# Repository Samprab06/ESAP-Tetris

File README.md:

# ESAP Tetris

A complete, feature-packed Tetris game implementation for the ESP32 microcontroller featuring a custom PCB design, real-time graphics rendering on an ILI9341 SPI TFT display, I2S audio playback, SD card asset loading and a future multiplayer implementation

---

##  PCB Design

The project features a custom-designed PCB tailored for handheld gameplay with optimized power delivery, hardware debouncing, and an auto-programming USB-C interface.

### Board Renders

| Back View (Component Side) | Front View (Controls) |
| :---: | :---: |
|  |  |

### Key Hardware & Schematic Highlights

- **Microcontroller**: ESP32-WROOM-32 module (32-bit dual-core Xtensa @ 240 MHz, 520 KB SRAM, Wi-Fi/BT).
- **USB-C Interface & Auto-Flashing**: Integrated `CH340C` USB-to-UART converter with dual NPN auto-reset circuitry (`MUN5211DW1`) for seamless hands-free code uploads via USB Type-C.
- **Power Management**: `AP2112K-3.3` LDO regulator supplying up to 600mA at 3.3V with dedicated ground plane thermal heat sinking. USB Type-C `CC1`/`CC2` 5.1kΩ pull-down resistors for 5V C-to-C charger support.
- **Display Connection**: Dedicated 14-pin socket header for 2.8" ILI9341 SPI TFT Display (240×320 resolution) on the `VSPI` bus. Includes 10kΩ pull-up resistor on `CS` (`GPIO5`).
- **SD Card Storage**: 4-pin SPI socket header for MicroSD card module on the `HSPI` bus. Includes 10kΩ pull-up resistor on `CS` (`GPIO15`).
- **Input Controllers**: 8 tactile pushbuttons (UP, DOWN, LEFT, RIGHT, A, B, START, SELECT) with hardware RC debouncing filters (0.1µF capacitors) and 10kΩ pull-up resistors on input-only GPIOs (34, 35, 36, 39).
- **Audio & Volume Control**: Audio output header with an integrated slide switch (`SW12`) for hardware gain/volume control.

---

## 🛠️ Hardware Specifications & Pinout

### SPI Display Connection (VSPI)

| ESP32 Pin | Signal Name | Display Function |
| :--- | :--- | :--- |
| **GPIO 23** | `MOSI` | Serial Data Input |
| **GPIO 19** | `MISO` | Serial Data Output |
| **GPIO 18** | `SCK` | Serial Clock |
| **GPIO 5** | `CS` | Chip Select (10kΩ Pull-Up) |
| **GPIO 2** | `DC` | Data / Command Select |
| **GPIO 4** | `RST` | Reset |
| **3.3V** | `LED` | Display Backlight Power |

### MicroSD Card Connection (HSPI)

| ESP32 Pin | Signal Name | SD Card Function |
| :--- | :--- | :--- |
| **GPIO 13** | `MOSI` | Data Input |
| **GPIO 17** | `MISO` | Data Output |
| **GPIO 14** | `SCK` | Clock |
| **GPIO 15** | `CS` | Chip Select (10kΩ Pull-Up) |

### Game Control Buttons

| GPIO Pin | Function | Hardware Circuit |
| :--- | :--- | :--- |
| **GPIO 36 (VP)** | Left | 10kΩ Pull-Up + 0.1µF Debounce |
| **GPIO 39 (VN)** | Right | 10kΩ Pull-Up + 0.1µF Debounce |
| **GPIO 34** | Down | 10kΩ Pull-Up + 0.1µF Debounce |
| **GPIO 35** | Up / Rotate | 10kΩ Pull-Up + 0.1µF Debounce |
| **GPIO 32** | Button A | 10kΩ Pull-Up + 0.1µF Debounce |
| **GPIO 33** | Button B | 10kΩ Pull-Up + 0.1µF Debounce |
| **GPIO 27** | Start | 10kΩ Pull-Up + 0.1µF Debounce |
| **GPIO 16** | Select | 10kΩ Pull-Up + 0.1µF Debounce |

---

##  Software Architecture

The software is structured as a **PlatformIO** project 

```
ESAP_Tetris/
├── PCB/                     # KiCad 10 PCB schematics, board layouts & gerbers
│   ├── pcb_front.png
│   └── pcb_back.png
├── include/                 # Header files
│   ├── main.hpp
│   ├── logic.h
│   ├── display.h
│   ├── audio.h
│   └── sdcard.h
├── src/                     # Source implementations
│   ├── main.cpp             # FreeRTOS task initialization & main loop
│   ├── logic.cpp            # Tetris game rules & state machine
│   ├── display.cpp          # TFT graphics rendering
│   ├── audio.cpp            # I2S audio decoding & streaming
│   └── sdcard.cpp           # SD card file system interface
├── platformio.ini           # PlatformIO configuration
└── README.md                # Project documentation
```

---

##  Building & Flashing

### Prerequisites
- **VS Code** with **PlatformIO IDE** extension installed.

### Steps
1. Clone the repository:
   ```bash
   git clone https://github.com/Samprab06/ESAP-Tetris.git
   cd ESAP-Tetris
   ```
2. Connect your ESP32 board via USB-C.
3. Build & Upload firmware using PlatformIO:
   ```bash
   pio run -t upload
   ```
4. Open the Serial Monitor:
   ```bash
   pio device monitor
   ```

---

---

##  License

This project is open-source and provided for educational and personal use.

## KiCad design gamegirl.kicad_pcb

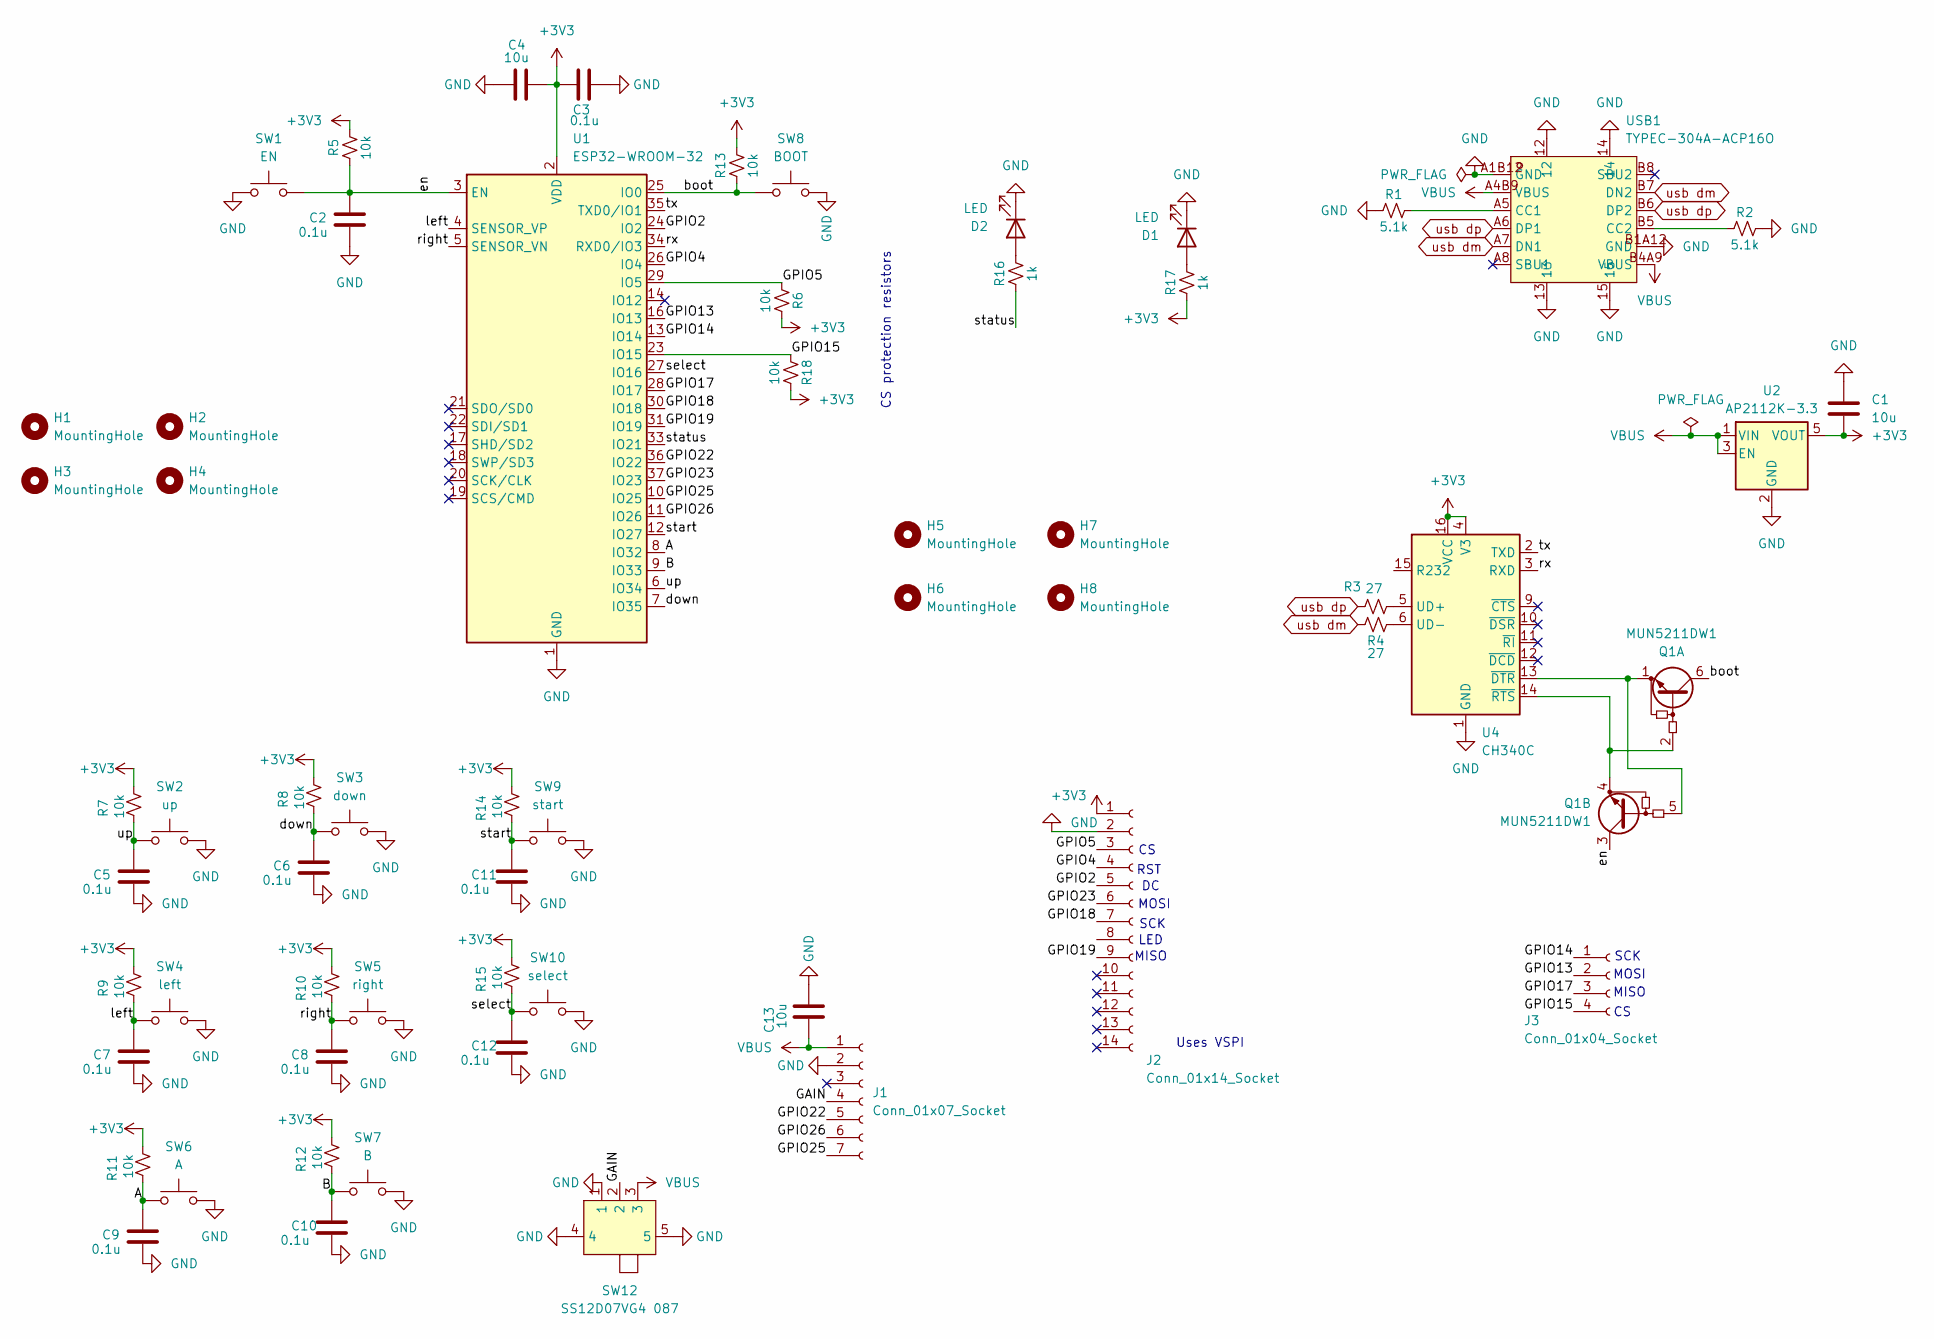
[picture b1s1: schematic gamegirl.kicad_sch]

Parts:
C1, C4, C13: 10u; C_0805_2012Metric
C2, C3, C5, C6, C7, C8, C9, C10, C11, C12: 0.1u; C_0805_2012Metric
D1, D2: LED; LED_0603_1608Metric
H1, H2, H3, H4: MountingHole; MountingHole_3.2mm_M3
H5, H6, H7, H8: MountingHole; MountingHole_3.2mm_M3_DIN965_Pad
J1: Conn_01x07_Socket; PinSocket_1x07_P2.54mm_Vertical
J2: Conn_01x14_Socket; PinSocket_1x14_P2.54mm_Vertical
J3: Conn_01x04_Socket; PinSocket_1x04_P2.54mm_Vertical
Q1: MUN5211DW1; SOT-363_SC-70-6
R1, R2: 5.1k; R_0805_2012Metric
R3, R4: 27; R_0603_1608Metric
R5, R6, R7, R8, R9, R10, R11, R12, R13, R14, R15, R18: 10k; R_0805_2012Metric
R16, R17: 1k; R_0805_2012Metric
SW1: EN; SW_PUSH_6mm
SW2: up; SW_PUSH_6mm
SW3: down; SW_PUSH_6mm
SW4: left; SW_PUSH_6mm
SW5: right; SW_PUSH_6mm
SW6: A; SW_PUSH_6mm
SW7: B; SW_PUSH_6mm
SW8: BOOT; SW_PUSH_6mm
SW9: start; SW_PUSH_6mm
SW10: select; SW_PUSH_6mm
SW12: SS12D07VG4 087; SW-TH_SS12D07VG4; MPN SS12D07VG4 087; LCSC Part C2939726
U1: ESP32-WROOM-32
U2: AP2112K-3.3; SOT-23-5
U4: CH340C; SOIC-16_3.9x9.9mm_P1.27mm
USB1: TYPEC-304A-ACP16O; USB-SMD_TYPEC-304A-ACP16O; MPN TYPEC-304A-ACP16O; LCSC Part C2909610

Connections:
+3V3: C1.2, C3.1, C4.2, J2.1, R5.2, R6.2, R7.2, R8.2, R9.2, R10.2, R11.2, R12.2, R13.2, R14.2, R15.2, R17.1, R18.2, U1.2 (VDD), U2.5 (VOUT), U4.4 (V3), U4.16 (VCC)
/A: C9.1, R11.1, SW6.1, U1.8 (IO32)
/B: C10.1, R12.1, SW7.1, U1.9 (IO33)
/GAIN: J1.4, SW12.2
/GPIO2: J2.5, U1.24 (IO2)
/GPIO4: J2.4, U1.26 (IO4)
/GPIO5: J2.3, R6.1, U1.29 (IO5)
/GPIO13: J3.2, U1.16 (IO13)
/GPIO14: J3.1, U1.13 (IO14)
/GPIO15: J3.4, R18.1, U1.23 (IO15)
/GPIO17: J3.3, U1.28 (IO17)
/GPIO18: J2.7, U1.30 (IO18)
/GPIO19: J2.9, U1.31 (IO19)
/GPIO22: J1.5, U1.36 (IO22)
/GPIO23: J2.6, U1.37 (IO23)
/GPIO25: J1.7, U1.10 (IO25)
/GPIO26: J1.6, U1.11 (IO26)
/boot: Q1.6 (C1), R13.1, SW8.1, U1.25 (IO0)
/down: C6.1, R8.1, SW3.1, U1.7 (IO35)
/en: C2.1, Q1.3 (C2), R5.1, SW1.2, U1.3 (EN)
/left: C7.1, R9.1, SW4.1, U1.4 (SENSOR_VP)
/right: C8.1, R10.1, SW5.1, U1.5 (SENSOR_VN)
/rx: U1.34 (RXD0/IO3), U4.3 (RXD)
/select: C12.1, R15.1, SW10.1, U1.27 (IO16)
/start: C11.1, R14.1, SW9.1, U1.12 (IO27); also elsewhere on the board
/status: R16.1, U1.33 (IO21)
/tx: U1.35 (TXD0/IO1), U4.2 (TXD)
/up: C5.1, R7.1, SW2.1, U1.6 (IO34)
GND: C1.1, C2.2, C3.2, C4.1, C5.2, C6.2, C7.2, C8.2, C9.2, C10.2, C11.2, C12.2, C13.2, D1.1 (K), D2.1 (K), J1.2, J2.2, R1.1, R2.2, SW1.1, SW2.2, SW3.2, SW4.2, SW5.2, SW6.2, SW7.2, SW8.2, SW9.2, SW10.2, SW12.1, SW12.4, SW12.5, U1.1 (GND), U1.15 (GND), U1.38 (GND), U1.39 (GND), U2.2 (GND), U4.1 (GND), USB1.12, USB1.13, USB1.14, USB1.15, USB1.A1B12 (GND), USB1.B1A12 (GND); also elsewhere on the board
unnamed: D1.2 (A), R17.2
unnamed: D2.2 (A), R16.2
unnamed: Q1.2 (B1), Q1.4 (E2), U4.14 (~RTS)
unnamed: Q1.1 (E1), Q1.5 (B2), U4.13 (~DTR)
unnamed: R3.2, U4.5 (UD+)
unnamed: R4.2, U4.6 (UD-)
unnamed: R1.2, USB1.A5 (CC1)
unnamed: R2.1, USB1.B5 (CC2)
VBUS: C13.1, J1.1, SW12.3, U2.1 (VIN), U2.3 (EN), USB1.A4B9 (VBUS), USB1.B4A9 (VBUS)
usb dm: R4.1, USB1.A7 (DN1), USB1.B7 (DN2)
usb dp: R3.1, USB1.A6 (DP1), USB1.B6 (DP2)

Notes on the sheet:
MISO
SCK
CS protection resistors
Uses VSPI
MOSI
LED
RST

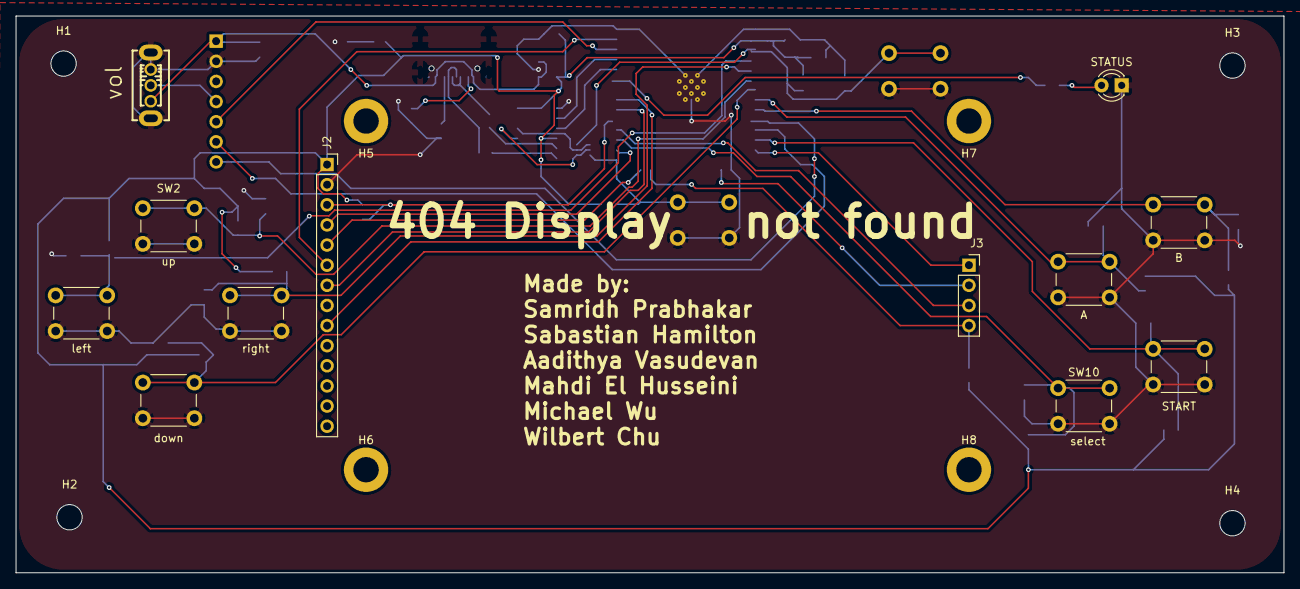
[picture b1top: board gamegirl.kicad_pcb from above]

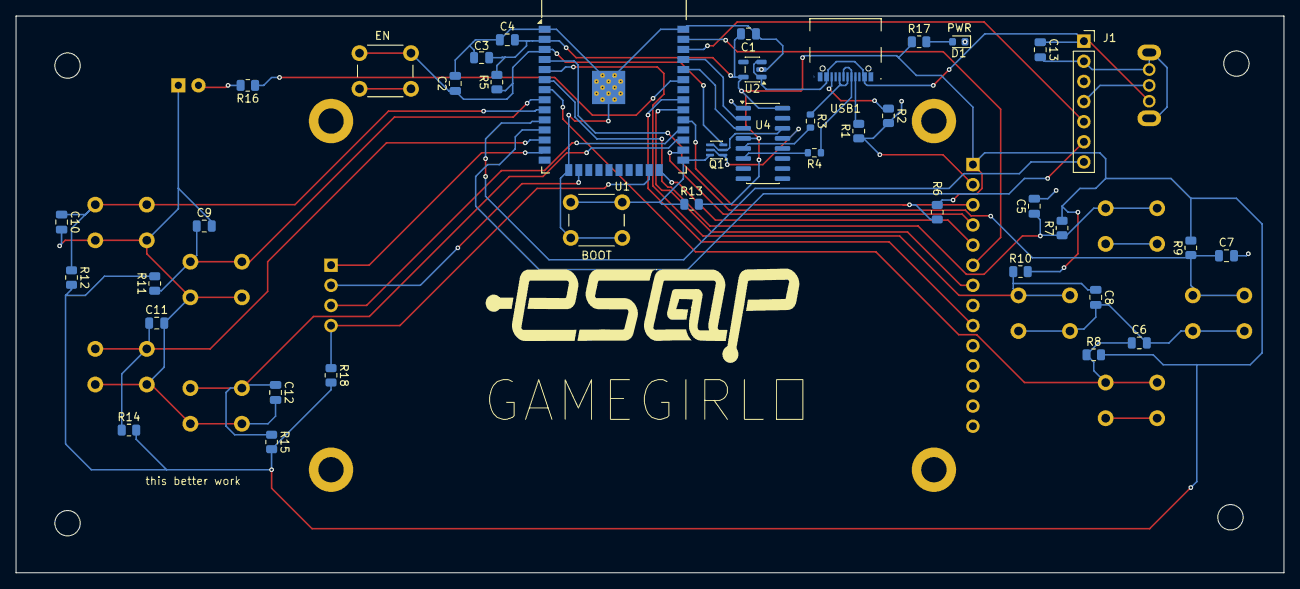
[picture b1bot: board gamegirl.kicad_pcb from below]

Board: 2 copper layers, 160.0 x 70.2 mm, 60 parts (40 on the bottom side), 40 nets.

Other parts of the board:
START: start; SW_PUSH_6mm

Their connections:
/start: START.1; also elsewhere on the board
GND: START.2; also elsewhere on the board

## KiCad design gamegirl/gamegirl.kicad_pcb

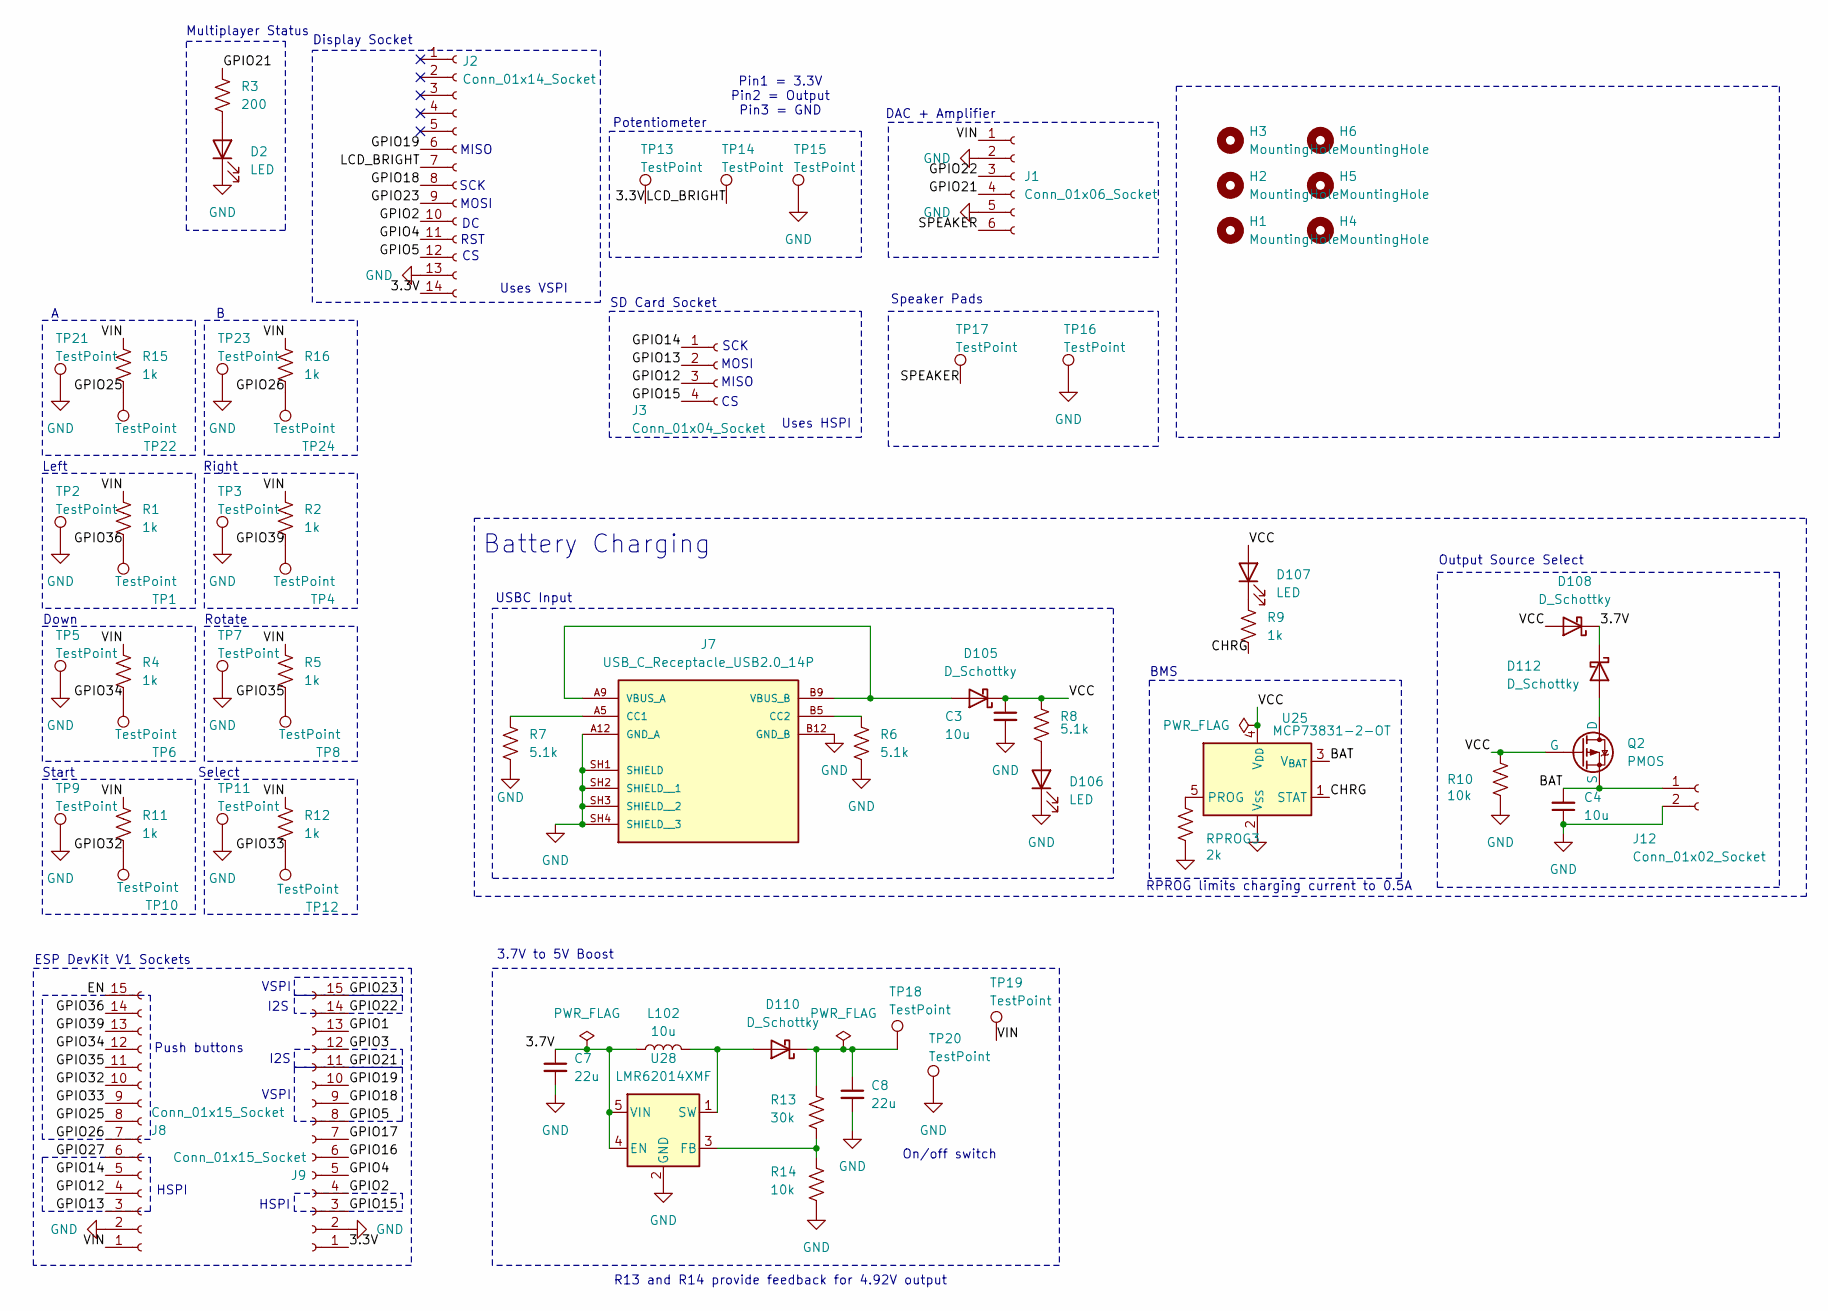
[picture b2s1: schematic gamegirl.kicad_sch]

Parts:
C3, C4: 10u; C_0603_1608Metric; LCSC C19702
C7, C8: 22u; C_0805_2012Metric; LCSC C45783
D2: LED; LED_0603_1608Metric
D105, D108, D110, D112: D_Schottky; D_SOD-323; LCSC C191023
D106: LED; LED_0603_1608Metric; LCSC C2286
D107: LED; LED_0603_1608Metric; LCSC C2297
H1, H2, H3, H4, H5, H6: MountingHole; MountingHole_2.2mm_M2_ISO14580
J1: Conn_01x06_Socket; PinHeader_1x06_P2.54mm_Vertical
J2: Conn_01x14_Socket; PinHeader_1x14_P2.54mm_Vertical
J3: Conn_01x04_Socket; PinHeader_1x04_P2.54mm_Vertical
J7: USB_C_Receptacle_USB2.0_14P; AMPHENOL_10164359-00011LF; PARTREV A; LCSC C5407555
J8, J9: Conn_01x15_Socket; PinSocket_1x15_P2.54mm_Vertical
J12: Conn_01x02_Socket; JST_PH_S2B-PH-K_1x02_P2.00mm_Horizontal; LCSC C157955
L102: 10u; L_Sunlord_SWPA4020S; LCSC C82398
Q2: PMOS; SOT-23; LCSC C15127
R1, R2, R4, R5, R11, R12, R15, R16: 1k; R_0603_1608Metric
R3: 200; R_0603_1608Metric
R6, R7, R8: 5.1k; R_0603_1608Metric; LCSC C23186
R9: 1k; R_0603_1608Metric; LCSC C4410
R10, R14: 10k; R_0603_1608Metric; LCSC C17414
R13: 30k; R_0603_1608Metric; LCSC C17621
RPROG3: 2k; R_0603_1608Metric; LCSC C17944
TP1, TP2, TP3, TP4, TP5, TP6, TP7, TP8, TP9, TP10, TP11, TP12, TP13, TP14, TP15, TP16, TP17, TP18, TP19, TP20, TP21, TP22, TP23, TP24: TestPoint; TestPoint_Pad_D2.0mm
U25: MCP73831-2-OT; SOT-23-5; LCSC C14879
U28: LMR62014XMF; SOT-23-5; LCSC C468235

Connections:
/3.3V: J2.14, J9.1, TP13.1
/3.7V: C7.1, D108.1 (K), D112.1 (K), L102.1, U28.4 (EN), U28.5 (VIN)
/BAT: C4.2, J12.1, Q2.3 (S), U25.3 (V_{BAT})
/CHRG: R9.2, U25.1 (STAT)
/EN: J8.15
/GPIO1: J9.13
/GPIO2: J2.10, J9.4
/GPIO3: J9.12
/GPIO4: J2.11, J9.5
/GPIO5: J2.12, J9.8
/GPIO12: J3.3, J8.4
/GPIO13: J3.2, J8.3
/GPIO14: J3.1, J8.5
/GPIO15: J3.4, J9.3
/GPIO16: J9.6
/GPIO17: J9.7
/GPIO18: J2.8, J9.9
/GPIO19: J2.6, J9.10
/GPIO21: J1.4, J9.11, R3.2
/GPIO22: J1.3, J9.14
/GPIO23: J2.9, J9.15
/GPIO25: J8.8, R15.2, TP22.1
/GPIO26: J8.7, R16.2, TP24.1
/GPIO27: J8.6
/GPIO32: J8.10, R11.2, TP10.1
/GPIO33: J8.9, R12.2, TP12.1
/GPIO34: J8.12, R4.2, TP6.1
/GPIO35: J8.11, R5.2, TP8.1
/GPIO36: J8.14, R1.2, TP1.1
/GPIO39: J8.13, R2.2, TP4.1
/LCD_BRIGHT: J2.7, TP14.1
/SPEAKER: J1.6, TP17.1
/VCC: C3.1, D105.1 (K), D107.2 (A), D108.2 (A), Q2.2 (G), R8.1, R10.1, U25.4 (V_{DD})
/VIN: J1.1, J8.1, R1.1, R2.1, R4.1, R5.1, R11.1, R12.1, R15.1, R16.1, TP19.1
GND: C3.2, C4.1, C7.2, C8.2, D2.1 (K), D106.1 (K), J1.2, J1.5, J2.13, J7.A12 (GND_A), J7.B12 (GND_B), J7.SH1 (SHIELD), J7.SH2 (SHIELD__1), J7.SH3 (SHIELD__2), J7.SH4 (SHIELD__3), J8.2, J9.2, J12.2, R6.2, R7.2, R10.2, R14.2, RPROG3.2, TP2.1, TP3.1, TP5.1, TP7.1, TP9.1, TP11.1, TP15.1, TP16.1, TP20.1, TP21.1, TP23.1, U25.2 (V_{SS}), U28.2 (GND)
unnamed: D2.2 (A), R3.1
unnamed: D105.2 (A), J7.A9 (VBUS_A), J7.B9 (VBUS_B)
unnamed: D106.2 (A), R8.2
unnamed: D107.1 (K), R9.1
unnamed: D110.2 (A), L102.2, U28.1 (SW)
unnamed: C8.1, D110.1 (K), R13.1, TP18.1
unnamed: D112.2 (A), Q2.1 (D)
unnamed: J7.A5 (CC1), R7.1
unnamed: J7.B5 (CC2), R6.1
unnamed: RPROG3.1, U25.5 (PROG)
unnamed: R13.2, R14.1, U28.3 (FB)

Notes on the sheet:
BMS
MISO
RPROG limits charging current to 0.5A
Multiplayer Status
Left
HSPI
Uses HSPI
Select
VSPI
Down
SD Card Socket
DAC + Amplifier
USBC Input
Battery Charging
Push buttons
R13 and R14 provide feedback for 4.92V output
3.7V to 5V Boost
RST
Potentiometer
Rotate
Output Source Select
MOSI
Uses VSPI
Speaker Pads
Pin1 = 3.3V Pin2 = Output Pin3 = GND
Right
On/off switch
I2S
SCK
Display Socket
ESP DevKit V1 Sockets
Start

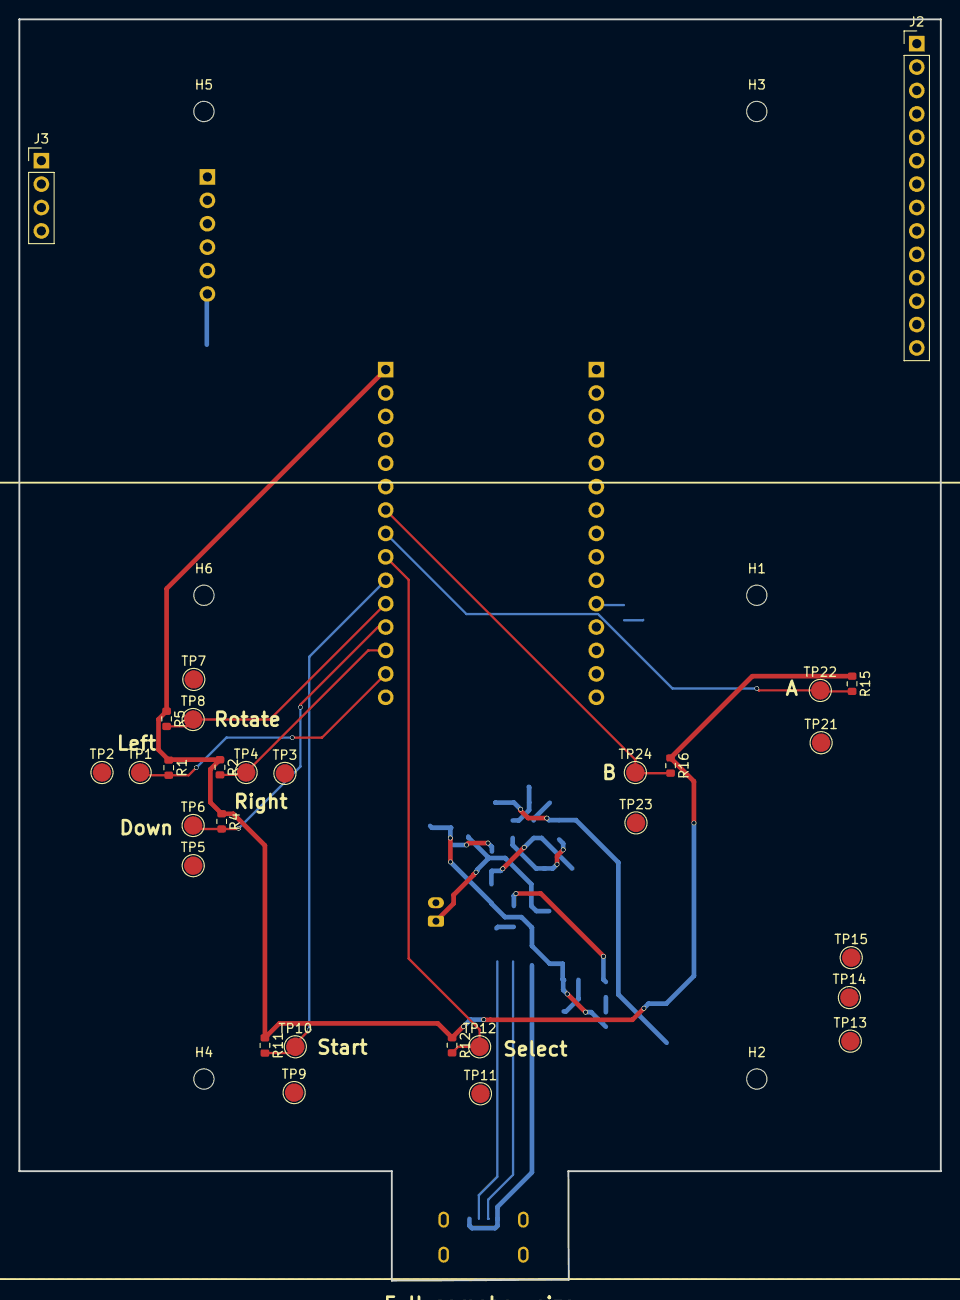
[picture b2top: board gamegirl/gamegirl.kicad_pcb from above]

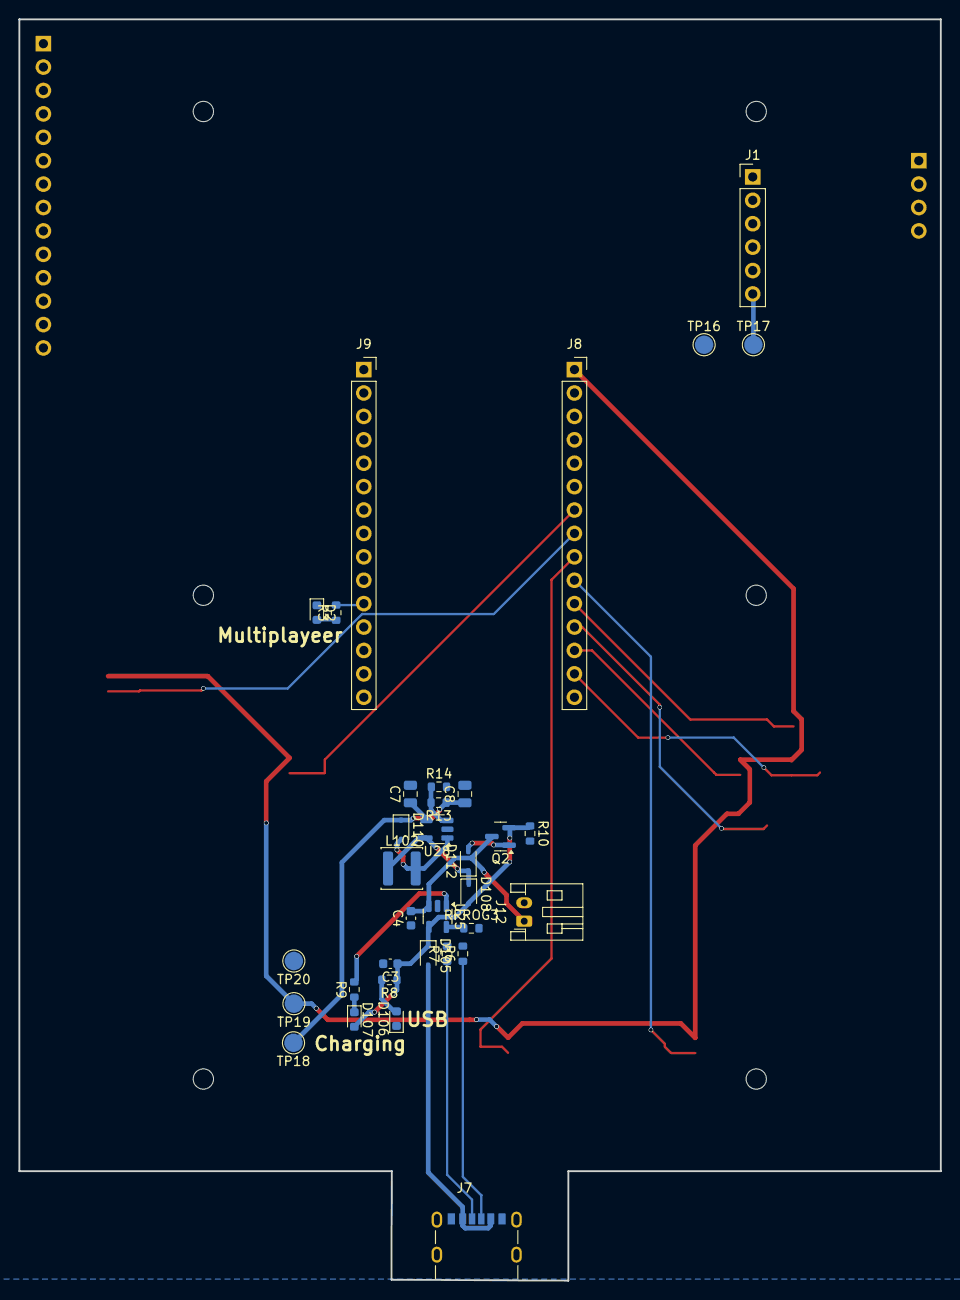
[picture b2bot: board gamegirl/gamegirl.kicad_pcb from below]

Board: 2 copper layers, 100.0 x 136.9 mm, 69 parts (34 on the bottom side), 40 nets.

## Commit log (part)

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2026-04-12 working? logic
2026-04-12 added start button fixed text not working
2026-04-12 added libraries
2026-04-12 added sd
2026-04-12 copied sd card from example
2026-04-12 broken af libraries
2026-04-13 Convert TFT_eSPI from repo to regular folder
2026-04-13 arduino
2026-04-13 Force track arduino-esp32 directory
2026-04-29 pls work
